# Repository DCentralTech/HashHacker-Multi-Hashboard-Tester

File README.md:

# HashHacker-Multi-Hashboard-Tester
HashHacker Multi-Hashboard Tester from D-Central, the ultimate open-source tool for repairing and testing your ASIC miners. We plan features such as advanced and intuitive interface, the HashHacker Multi-Hashboard Tester is designed to help you quickly and easily diagnose and fix any issues with your mining hardware.

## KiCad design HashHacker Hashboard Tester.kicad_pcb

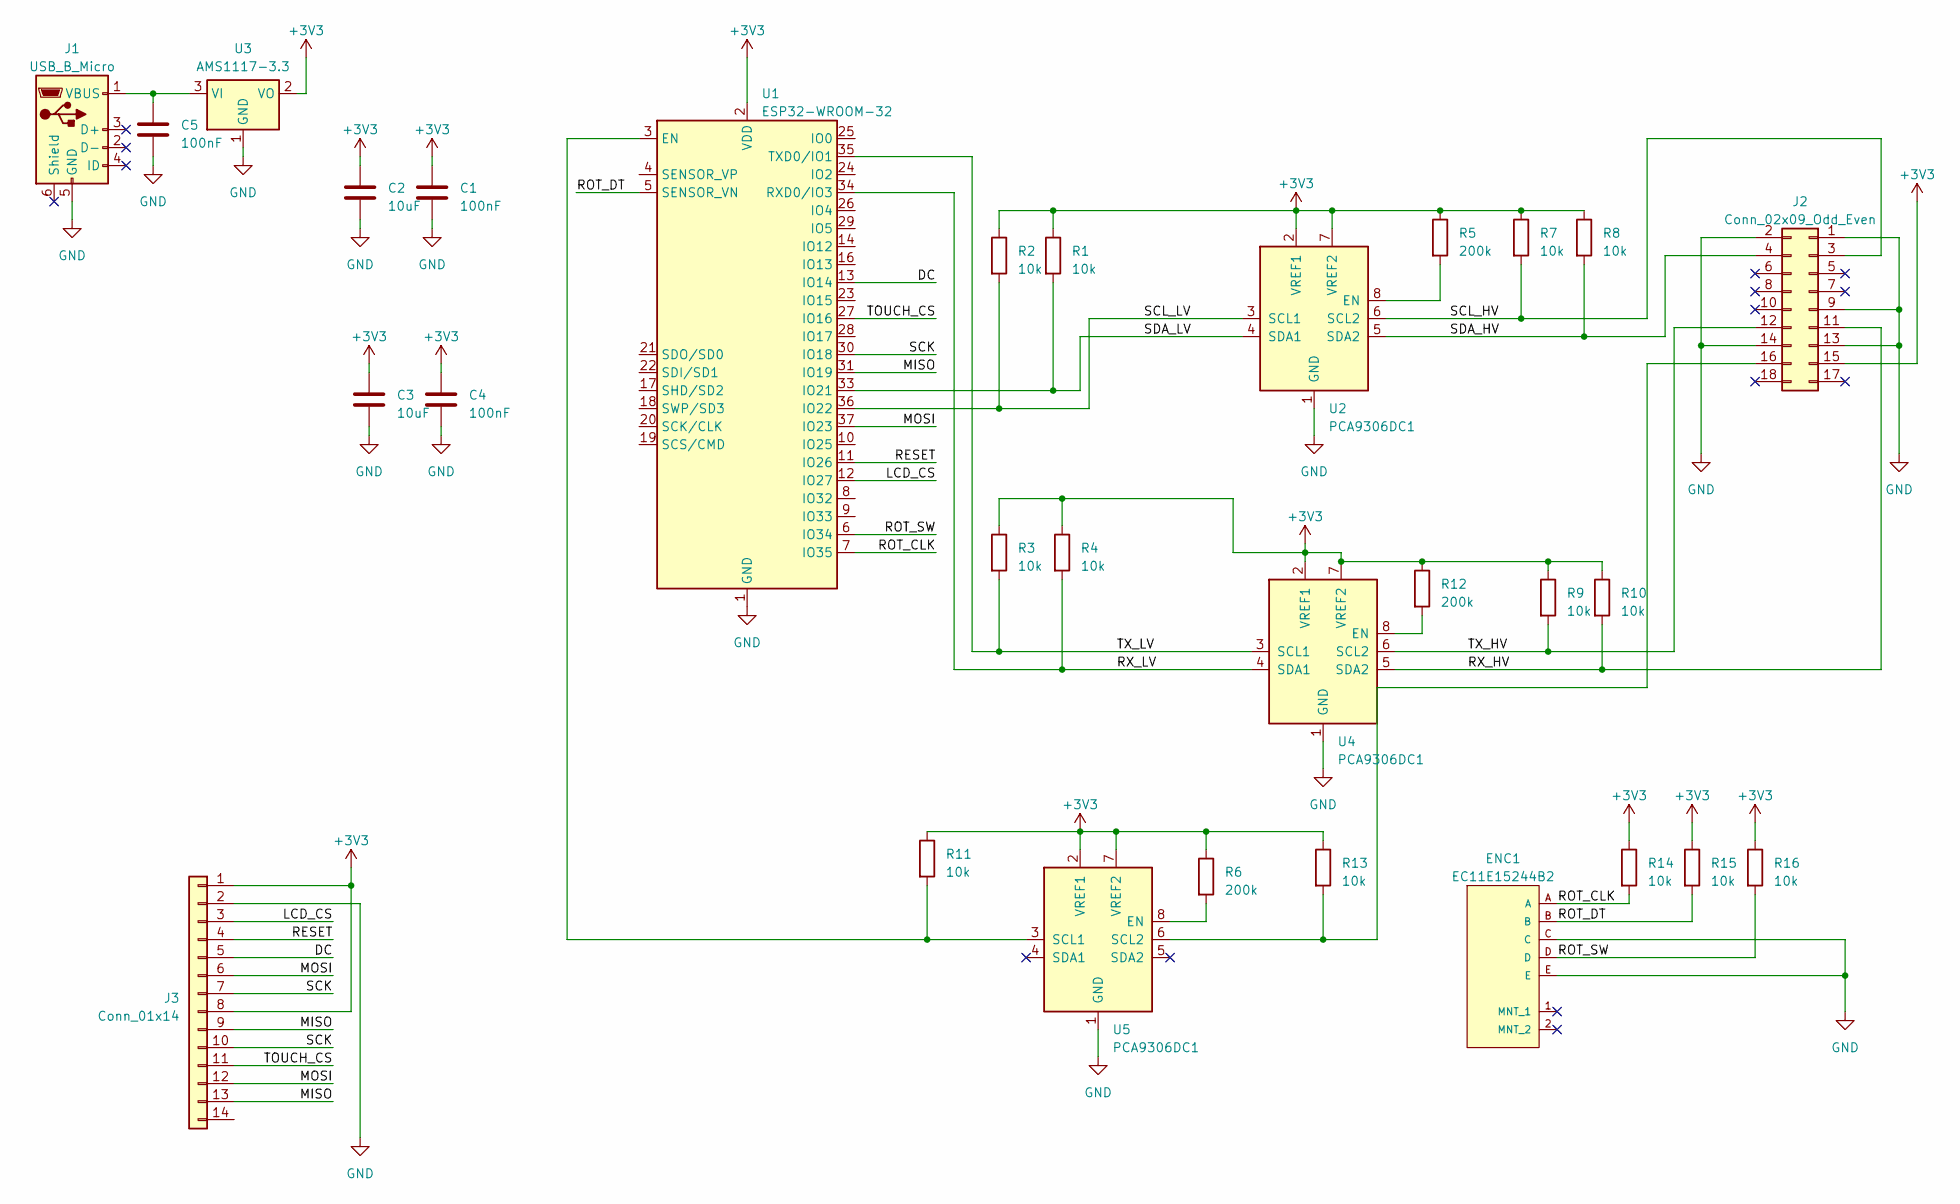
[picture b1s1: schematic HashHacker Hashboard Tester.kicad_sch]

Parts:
C1, C4, C5: 100nF; C_0402_1005Metric; Manufacturer P/N CL05B104KB54PNC; LCSC P/N C307331
C2, C3: 10uF; C_0402_1005Metric; Manufacturer P/N CL05A106MQ5NUNC; LCSC P/N C15525
ENC1: EC11E15244B2; ALPS-EC11E15244B2-0; Ratings 10mA 5V DC; mouser part number 688-EC11E15244B2
J1: USB_B_Micro; USB_Micro-AB_Molex_47590-0001; Manufacturer P/N 475900001; LCSC P/N C136001
J2: Conn_02x09_Odd_Even; PinSocket_2x09_P2.00mm_Vertical
J3: Conn_01x14; PinSocket_1x14_P2.54mm_Vertical; Manufacturer P/N PM254-1-14-Z-8.5; LCSC P/N C2897377
R1, R2, R3, R4, R7, R8, R9, R10, R11, R13, R14, R15, R16: 10k; R_0402_1005Metric; Manufacturer P/N 0402WGF100KTCE; LCSC P/N C25086
R5, R6, R12: 200k; R_0402_1005Metric; Manufacturer P/N 0402WGF2003TCE; LCSC P/N C25764
U1: ESP32-WROOM-32; Manufacturer P/N ESP32-WROOM-32-N4; LCSC P/N C82899
U2, U4, U5: PCA9306DC1; VSSOP-8_2.3x2mm_P0.5mm; Manufacturer P/N PCA9306DC1; LCSC P/N C129510
U3: AMS1117-3.3; SOT-223-3_TabPin2; Manufacturer P/N AMS1117-3.3; LCSC P/N C6186

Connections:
+3V3: C1.1, C2.1, C3.1, C4.1, J2.15, J3.1, J3.8, R1.1, R2.1, R3.1, R4.1, R5.1, R6.1, R7.1, R8.1, R9.1, R10.1, R11.1, R12.1, R13.1, R14.1, R15.1, R16.1, U1.2 (VDD), U2.2 (VREF1), U2.7 (VREF2), U3.2 (VO), U4.2 (VREF1), U4.7 (VREF2), U5.2 (VREF1), U5.7 (VREF2)
/DC: J3.5, U1.13 (IO14)
/LCD_CS: J3.3, U1.12 (IO27)
/MISO: J3.9, J3.13, U1.31 (IO19)
/MOSI: J3.6, J3.12, U1.37 (IO23)
/RESET: J3.4, U1.11 (IO26)
/ROT_CLK: ENC1.A, R14.2, U1.7 (IO35)
/ROT_DT: ENC1.B, R15.2, U1.5 (SENSOR_VN)
/ROT_SW: ENC1.D, R16.2, U1.6 (IO34)
/RX_HV: J2.11, R10.2, U4.5 (SDA2)
/RX_LV: R4.2, U1.34 (RXD0/IO3), U4.4 (SDA1)
/SCK: J3.7, J3.10, U1.30 (IO18)
/SCL_HV: J2.3, R7.2, U2.6 (SCL2)
/SCL_LV: R2.2, U1.36 (IO22), U2.3 (SCL1)
/SDA_HV: J2.4, R8.2, U2.5 (SDA2)
/SDA_LV: R1.2, U1.33 (IO21), U2.4 (SDA1)
/TOUCH_CS: J3.11, U1.27 (IO16)
/TX_HV: J2.12, R9.2, U4.6 (SCL2)
/TX_LV: R3.2, U1.35 (TXD0/IO1), U4.3 (SCL1)
GND: C1.2, C2.2, C3.2, C4.2, C5.2, ENC1.C, ENC1.E, J1.5 (GND), J2.1, J2.2, J2.9, J2.13, J2.14, J3.2, U1.1 (GND), U1.15 (GND), U1.38 (GND), U1.39 (GND), U2.1 (GND), U3.1 (GND), U4.1 (GND), U5.1 (GND)
unnamed: C5.1, J1.1 (VBUS), U3.3 (VI)
unnamed: J2.16, R13.2, U5.6 (SCL2)
unnamed: R11.2, U1.3 (EN), U5.3 (SCL1)
unnamed: R5.2, U2.8 (EN)
unnamed: R12.2, U4.8 (EN)
unnamed: R6.2, U5.8 (EN)

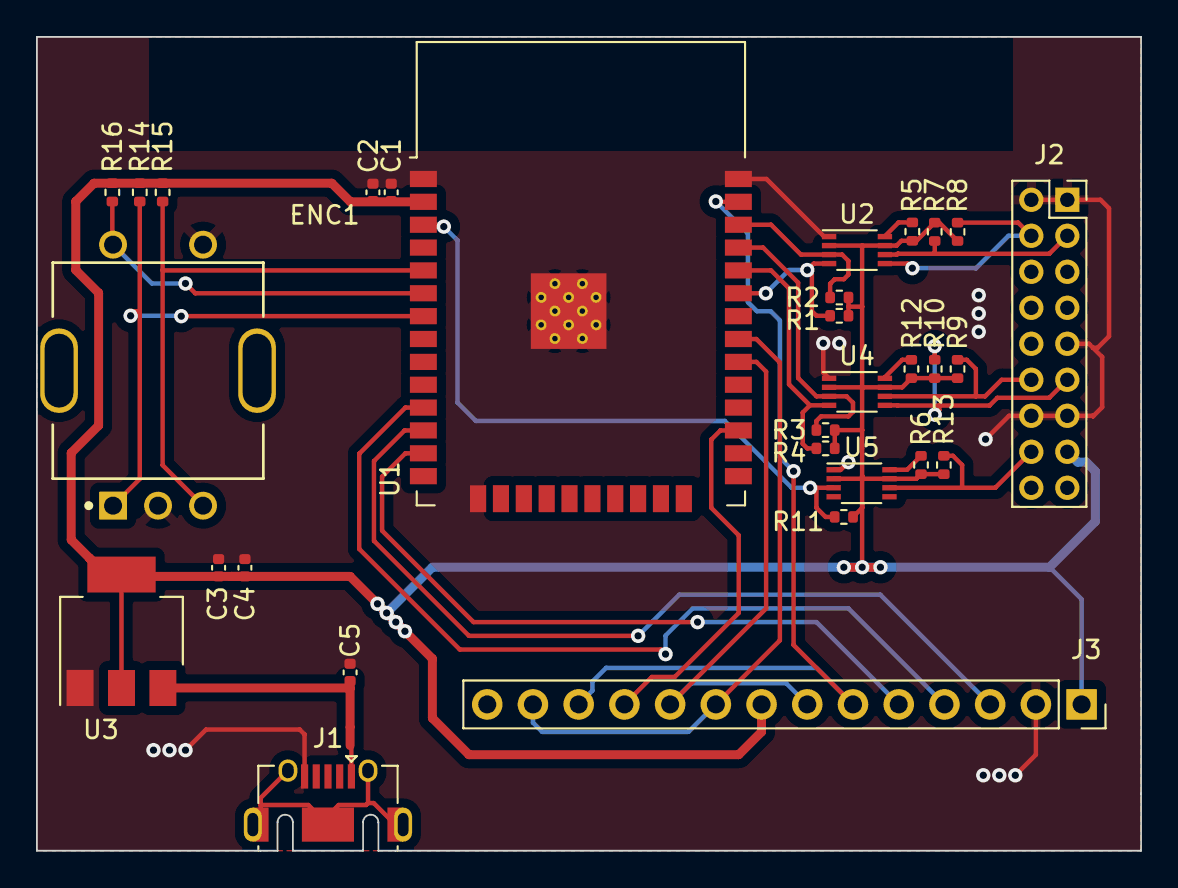
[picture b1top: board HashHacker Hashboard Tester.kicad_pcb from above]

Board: 2 copper layers, 61.3 x 45.2 mm, 30 parts (0 on the bottom side), 26 nets.
